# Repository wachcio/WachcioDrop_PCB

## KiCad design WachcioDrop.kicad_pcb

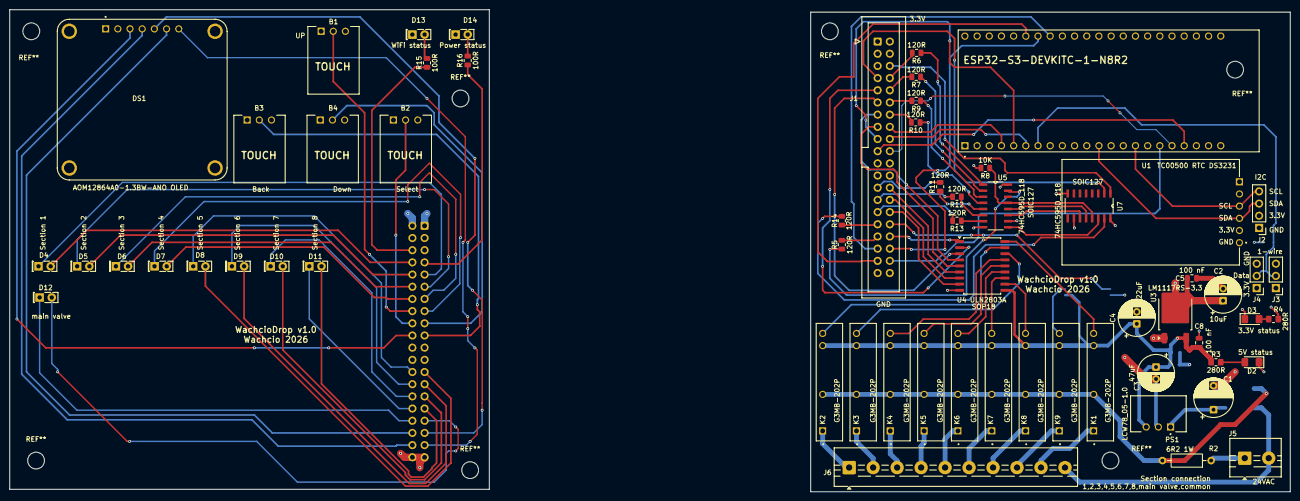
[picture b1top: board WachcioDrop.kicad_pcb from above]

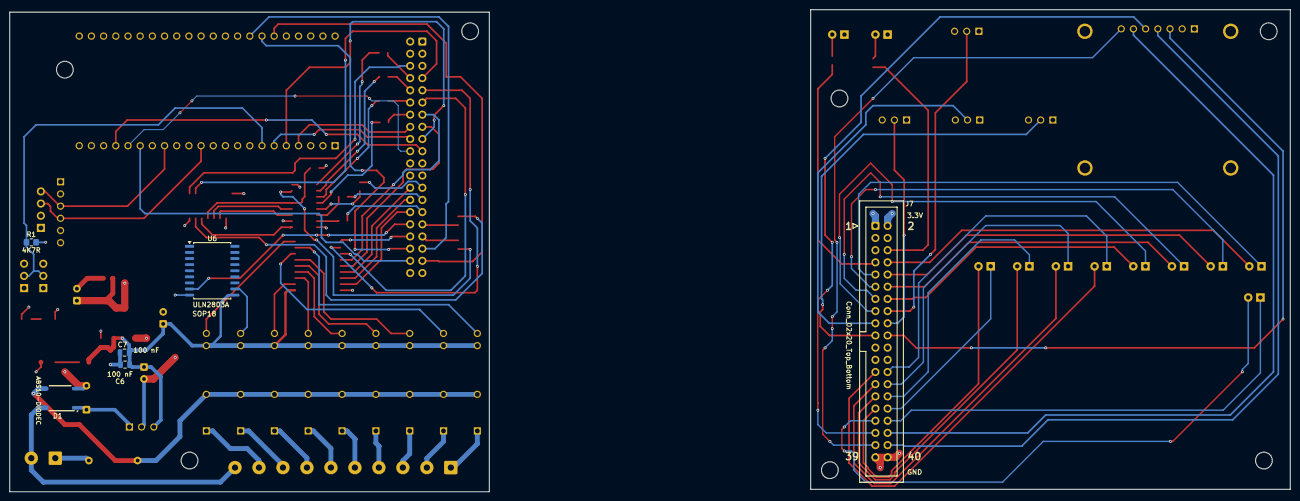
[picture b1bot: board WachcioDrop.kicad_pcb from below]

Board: 4 copper layers, 267.0 x 100.5 mm, 67 parts (6 on the bottom side), 103 nets.

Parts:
B1, B2, B3, B4: Module_touch_sensor_TTP223
C1: C_Polarized; CP_Radial_D8.0mm_P5.00mm
C2: 10uF; CP_Radial_D7.5mm_P2.50mm
C3: 47uF; CP_Radial_D7.5mm_P2.50mm
C4: 22uF; CP_Radial_D7.5mm_P2.50mm
C5, C6, C7, C8: 100 nF; C_0805_2012Metric
D1: ABS10-DIODEC; Diode_Bridge_Diotec_ABS
D2, D3: LED; LED_1206_3216Metric_Pad1.42x1.75mm_HandSolder
D4, D5, D6, D7, D8, D9, D10, D11, D12, D14: LED; LED_Rectangular_W5.0mm_H2.0mm
D13: LED niebieski; LED_Rectangular_W5.0mm_H2.0mm
DS1: AOM12864A0-1.3BW-ANO OLED; LCD_AOM12864A0-1.3BW-ANO
J1, J7: Conn_02x20_Top_Bottom; IDC-Header_2x20_P2.54mm_Vertical
J2: Conn_01x04; PinHeader_1x04_P2.54mm_Vertical
J3, J4: Conn_01x03; PinHeader_1x03_P2.54mm_Vertical
J5: Screw_Terminal_01x02; TerminalBlock_MaiXu_MX126-5.0-02P_1x02_P5.00mm
J6: Conn_01x10_Socket; TerminalBlock_MaiXu_MX126-5.0-10P_1x10_P5.00mm
K1, K2, K3, K4, K5, K6, K7, K8, K9: G3MB-202P; RELAY_G3MB-202P
PS1: LCW78_05-1.0; CONV_LCW78_05-1.0
R1: 4K7R; R_0805_2012Metric_Pad1.20x1.40mm_HandSolder
R2: 6R2 1W; R_Axial_DIN0207_L6.3mm_D2.5mm_P10.16mm_Horizontal
R3, R4: 280R; R_0805_2012Metric_Pad1.20x1.40mm_HandSolder
R5, R6, R7, R9, R10, R11, R12, R13, R14: 120R; R_0805_2012Metric
R8: 10K; R_0805_2012Metric
R15, R16: 100R; R_0805_2012Metric
U1: TC00500 RTC DS3231; MODULE_TC00500
U2: ESP32-S3-DEVKITC-1-N8R2; XCVR_ESP32-S3-DEVKITC-1-N8R2
U3: LM1117RS-3.3; TO-252-2
U4, U6: ULN2803A; SOP-18_7.495x11.515mm_P1.27mm
U5, U7: 74HC595D_118; SOIC127P600X175-16N

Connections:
+3.3V: B1.1 (VCC), B2.1 (VCC), B3.1 (VCC), B4.1 (VCC), C2.1, C5.2, DS1.2 (VDD), J1.1, J1.2, J2.2, J3.1, J4.1, J7.1, J7.2, R1.2, R4.1, R8.2, U1.5 (VCC), U2.J1_1 (3V3), U2.J1_2 (3V3), U3.2 (VO), U5.10 (~MR), U5.16 (VCC), U7.10 (~MR), U7.16 (VCC)
+5V: C3.1, C4.1, C6.2, C7.2, C8.2, K1.3, K2.3, K3.3, K4.3, K5.3, K6.3, K7.3, K8.3, K9.3, PS1.3 (+VOUT), R3.1, U3.3 (VI), U4.10 (COM), U6.10 (COM)
/Główny/AC_common_N: D1.4, J5.2, J6.10
/Główny/PIN_BTN_BACK: J1.19, U2.J1_19 (GPIO13)
/Główny/PIN_BTN_DOWN: J1.17, U2.J1_5 (GPIO5)
/Główny/PIN_BTN_SELECT: J1.18, U2.J1_6 (GPIO6)
/Główny/PIN_BTN_UP: J1.16, U2.J1_4 (GPIO4)
/Główny/PIN_DS18B20: J3.2, J4.2, R1.1, U2.J1_7 (GPIO7)
/Główny/PIN_I2C_SCL: J2.4, U1.3 (SCL), U2.J1_15 (GPIO9)
/Główny/PIN_I2C_SDA: J2.3, U1.4 (SDA), U2.J1_12 (GPIO8)
/Główny/PIN_OLED_CLK: J1.20, U2.J1_18 (GPIO12)
/Główny/PIN_OLED_CS: J1.37, U2.J3_6 (MTMS/GPIO42)
/Główny/PIN_OLED_DC: J1.36, U2.J3_7 (MTDI/GPIO41)
/Główny/PIN_OLED_MOSI: J1.38, U2.J1_17 (GPIO11)
/Główny/PIN_OLED_RESET: J1.35, U2.J3_8 (MTDO/GPIO40)
/Główny/Shift_registers/595_OE: R8.1, U5.13 (~OE), U7.13 (~OE)
/Główny/Shift_registers/595_RCLK: U5.12 (ST_CP), U7.12 (ST_CP)
/Główny/Shift_registers/595_SRCLK: U5.11 (SH_CP), U7.11 (SH_CP)
/Główny/Shift_registers/595_komunikacja: U5.9 (Q7_2), U7.14 (DS)
/Główny/Shift_registers/AC_common: D1.3, K1.2, K2.2, K3.2, K4.2, K5.2, K6.2, K7.2, K8.2, K9.2, R2.2
/Główny/Shift_registers/AC_main_valve: J6.9, K1.1
/Główny/Shift_registers/AC_section1: J6.1, K2.1
/Główny/Shift_registers/AC_section2: J6.2, K3.1
/Główny/Shift_registers/AC_section3: J6.3, K4.1
/Główny/Shift_registers/AC_section4: J6.4, K5.1
/Główny/Shift_registers/AC_section5: J6.5, K6.1
/Główny/Shift_registers/AC_section6: J6.6, K7.1
/Główny/Shift_registers/AC_section7: J6.7, K8.1
/Główny/Shift_registers/AC_section8: J6.8, K9.1
/Główny/power_status: J1.7, U7.2 (Q2)
/Główny/section1_LED_A: J1.8, R6.2
/Główny/section1_LED_K: J1.9, U4.2 (I2)
/Główny/section2_LED_A: J1.10, R7.2
/Główny/section2_LED_K: J1.11, U4.3 (I3)
/Główny/section3_LED_A: J1.12, R9.2
/Główny/section3_LED_K: J1.13, U4.4 (I4)
/Główny/section4_LED_A: J1.14, R10.2
/Główny/section4_LED_K: J1.15, U4.5 (I5)
/Główny/section5_LED_A: J1.25, R11.2
/Główny/section5_LED_K: J1.26, U4.6 (I6)
/Główny/section6_LED_A: J1.27, R12.2
/Główny/section6_LED_K: J1.28, U4.7 (I7)
/Główny/section7_LED_A: J1.29, R13.2
/Główny/section7_LED_K: J1.30, U4.8 (I8)
/Główny/section8_LED_A: J1.31, R14.2
/Główny/section8_LED_K: J1.32, U6.8 (I8)
/Główny/wifi_status: J1.6, U7.1 (Q1)
/Główny/zaw_g_LED_A: J1.33, R5.2
/Główny/zaw_g_LED_K: J1.34, U4.1 (I1)
/Wyświetlacz/PIN_BTN_BACK: B3.2 (data), J7.19
/Wyświetlacz/PIN_BTN_DOWN: B4.2 (data), J7.17
/Wyświetlacz/PIN_BTN_SELECT: B2.2 (data), J7.18
/Wyświetlacz/PIN_BTN_UP: B1.2 (data), J7.16
/Wyświetlacz/PIN_OLED_CLK: DS1.3 (D0), J7.20
/Wyświetlacz/PIN_OLED_CS: DS1.7 (~CS), J7.37
/Wyświetlacz/PIN_OLED_DC: DS1.6 (DC), J7.36
/Wyświetlacz/PIN_OLED_MOSI: DS1.4 (D1), J7.38
/Wyświetlacz/PIN_OLED_RESET: DS1.5 (~RST), J7.35
/Wyświetlacz/power_status: J7.7, R16.1
/Wyświetlacz/section1_LED_A: D4.2 (A), J7.8
/Wyświetlacz/section1_LED_K: D4.1 (K), J7.9
/Wyświetlacz/section2_LED_A: D5.2 (A), J7.10
/Wyświetlacz/section2_LED_K: D5.1 (K), J7.11
/Wyświetlacz/section3_LED_A: D6.2 (A), J7.12
/Wyświetlacz/section3_LED_K: D6.1 (K), J7.13
/Wyświetlacz/section4_LED_A: D7.2 (A), J7.14
/Wyświetlacz/section4_LED_K: D7.1 (K), J7.15
/Wyświetlacz/section5_LED_A: D8.2 (A), J7.25
/Wyświetlacz/section5_LED_K: D8.1 (K), J7.26
/Wyświetlacz/section6_LED_A: D9.2 (A), J7.27
/Wyświetlacz/section6_LED_K: D9.1 (K), J7.28
/Wyświetlacz/section7_LED_A: D10.2 (A), J7.29
/Wyświetlacz/section7_LED_K: D10.1 (K), J7.30
/Wyświetlacz/section8_LED_A: D11.2 (A), J7.31
/Wyświetlacz/section8_LED_K: D11.1 (K), J7.32
/Wyświetlacz/wifi_status: J7.6, R15.1
/Wyświetlacz/zaw_g_LED_A: D12.2 (A), J7.33
/Wyświetlacz/zaw_g_LED_K: D12.1 (K), J7.34
GND: B1.3 (GND), B2.3 (GND), B3.3 (GND), B4.3 (GND), C1.2, C2.2, C3.2, C4.2, C5.1, C6.1, C7.1, C8.1, D1.2 (-), D2.1 (K), D3.1 (K), D13.1 (K), D14.1 (K), DS1.1 (GND), J1.39, J1.40, J2.1, J3.3, J4.3, J7.39, J7.40, PS1.2 (GND), U1.6 (GND), U2.J1_22 (GND), U2.J3_1 (GND), U2.J3_21 (GND), U2.J3_22 (GND), U3.1 (GND), U4.9 (GND), U5.8 (GND), U6.9 (GND), U7.8 (GND)
unnamed: C1.1, D1.1 (+), PS1.1 (+VIN)
unnamed: D2.2 (A), R3.2
unnamed: D3.2 (A), R4.2
unnamed: D13.2 (A), R15.2
unnamed: D14.2 (A), R16.2
unnamed: J5.1, R2.1
unnamed: K1.4, U4.18 (O1)
unnamed: K2.4, U4.17 (O2)
unnamed: K3.4, U4.16 (O3)
unnamed: K4.4, U4.15 (O4)
unnamed: K5.4, U4.14 (O5)
unnamed: K6.4, U4.13 (O6)
unnamed: K7.4, U4.12 (O7)
unnamed: K8.4, U4.11 (O8)
unnamed: R5.1, U5.15 (Q0)
unnamed: R6.1, U5.1 (Q1)
unnamed: R7.1, U5.2 (Q2)
unnamed: R9.1, U5.3 (Q3)
unnamed: R10.1, U5.4 (Q4)
unnamed: R11.1, U5.5 (Q5)
unnamed: R12.1, U5.6 (Q6)
unnamed: R13.1, U5.7 (Q7)
unnamed: K9.4, U6.11 (O8)
unnamed: R14.1, U7.15 (Q0)
